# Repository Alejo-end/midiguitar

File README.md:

# MIDI Guitar

A time-of-flight distance sensor embedded in a Squier Mustang electric guitar, turning hand gestures into MIDI messages for controlling effects in Max/MSP, Ableton, or any MIDI host.

## How it works

The system has two halves:

- **Guitar** (`code/tof_midi_v5/`): a VL53L1X sensor near the pickups measures hand distance. The firmware turns distance and hand speed into MIDI CC or 14-bit pitch bend, sends it over USB-MIDI, and broadcasts it over ESP-NOW (WiFi channel 1) to the receiver. A rotary encoder drives a 4-page OLED menu; a 16-LED NeoPixel ring mirrors the values.
- **Receiver dongle** (`code/tof_midi_v6_rx/`): receives the guitar's ESP-NOW stream and re-emits it as USB-MIDI and on a 5-pin DIN MIDI OUT. It also has its own VL53L5CX 8×8 sensor as a second gesture zone, an expression-pedal input and MUTE / HOLD footswitches.

## Firmware

| Folder | Runs on | Status |
|--------|---------|--------|
| **`code/tof_midi_v5/`** | Guitar (`finalMidiGuitar` PCB) | **Current.** USB-MIDI + ESP-NOW TX, 4-page UI, NVS settings, 8 presets, WiFi config page. See its [README](code/tof_midi_v5/README.md). |
| **`code/tof_midi_v6_rx/`** | Receiver dongle | **Current.** ESP-NOW RX → USB + DIN MIDI, local VL53L5CX, expression pedal, footswitches, pairing. |
| `code/tof_midi_v6/` | Receiver dongle | Experimental "Heat" build: mode router (DRONE / RHYTHM / DRUMS), MCP4561 expression output, presets, web config. Untested on hardware; ignores the dongle's expression input and HOLD footswitch. |
| `code/tof_midi_v4/` | Older guitar wiring | Legacy (BLE-MIDI, old pin map). Does **not** match the current PCB. |
| `code/debug/`, `code/debug_oled/` | Guitar PCB | Bring-up diagnostics (peripheral self-test, OLED-only test). |

## Wiring

XIAO ESP32-S3 pad → GPIO: `D0=1 D1=2 D2=3 D3=4 D4=5 D5=6 D6=43 D7=44 D8=7 D9=8 D10=9`

### Guitar (v5, `finalMidiGuitar` PCB)

| Function | XIAO pad | GPIO | Notes |
|----------|----------|------|-------|
| I2C SDA | D4 | 5 | OLED (0x3C) + VL53L1X (0x29), 400 kHz |
| I2C SCL | D5 | 6 | |
| NeoPixel data | D10 | 9 | Through level shifter U1 to the 16-LED ring |
| Encoder A | D8 | 7 | |
| Encoder B | D9 | 8 | |
| Encoder push | D3 | 4 | To GND, INPUT_PULLUP. All gestures are on this push. |
| SW1 | D2 | 3 | Populated but unused (reads stuck LOW on this PCB) |

The VL53L1X stays at its default address 0x29; the board has no XSHUT or INT trace.

### Receiver dongle (v6_rx, rev 2026-10)

| Function | XIAO pad | GPIO | Notes |
|----------|----------|------|-------|
| I2C SDA | D4 | 5 | OLED (0x3C) + VL53L5CX (0x29) [+ MCP4561 0x2E for v6] |
| I2C SCL | D5 | 6 | |
| NeoPixel data | D10 | 9 | Through level shifter to the 8-LED stick |
| Encoder A / B | D8 / D9 | 7 / 8 | |
| Encoder push | D3 | 4 | |
| MODE button S3 | D0 | 1 | To GND |
| MUTE button S4 + footswitch tip | D1 | 2 | To GND |
| Expression pedal wiper | D2 | 3 | ADC, internal pull-down |
| MIDI OUT (DIN) | D6 | 43 | Serial1 TX, 31250 baud |
| HOLD footswitch (ring) | D7 | 44 | To GND |

## Building

Arduino IDE or `arduino-cli`, board **XIAO_ESP32S3**, arduino-esp32 core 3.x.

- **USB Mode: USB-OTG (TinyUSB)** — required for USB-MIDI.
- **USB CDC On Boot: Enabled** for the dongle sketches. With it disabled, `Serial` runs on UART0, whose pins (GPIO 43/44) are the dongle's MIDI OUT and HOLD footswitch.

Libraries (Library Manager): Adafruit NeoPixel, Adafruit SSD1306, Adafruit GFX, plus **SparkFun VL53L1X** for the guitar or **SparkFun VL53L5CX** for the dongle.

```bash
arduino-cli compile -b esp32:esp32:XIAO_ESP32S3:USBMode=default,CDCOnBoot=cdc code/tof_midi_v5/
```

```bash
arduino-cli compile -b esp32:esp32:XIAO_ESP32S3:USBMode=default,CDCOnBoot=cdc code/tof_midi_v6_rx/
```

GitHub Actions (`.github/workflows/compile.yml`) compiles the v5, v6, v6_rx and debug sketches on every push.

After editing `code/tof_midi_v5/web_ui.html`, regenerate the embedded page with `code/tof_midi_v5/tools/build_web_ui.sh`.

## PCB

The guitar board is the KiCad project in `finalMidiGuitar/` (`finalMidiGuitar.kicad_sch`, `finalMidiGuitar.kicad_pcb`), with a STEP export and F.Cu + drill gerbers. `HARDWARE.md` documents an earlier iteration of the design and is out of date.

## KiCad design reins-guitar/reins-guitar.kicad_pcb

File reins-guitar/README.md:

# REINS guitar board for JLCPCB

This is the guitar board of the REINS system, made for JLCPCB. It replaces the milled board in `../finalMidiGuitar/`. These parts stay in the same places, in the same board coordinates: the outline, the four M2 holes, the OLED, the encoder, the button and the USB-C end of the XIAO. The pickguard cutouts and the mounting stay the same.

## What changed from the milled board

1. Two copper layers, a ground pour on both sides and stitching vias.
2. JLCPCB solders the small parts on the top side. The three cable headers stand on the bottom side, so the cables go down into the cavity.
3. A LiPo battery and an on/off switch. D0 reads the battery voltage, and the OLED shows the charge.
4. The LED ring also lights on battery. Two diodes feed it from USB 5 V or from the battery.
5. The button moved from D2 to D1 and uses two diagonal pads. On the milled board, the footprint joined both button pads to one internal contact of the switch. That is why D2 read stuck LOW.
6. The encoder tab slots follow the Bourns PEC12R sheet: 13.2 mm apart, 2.4 x 3.2 mm. The milled board had them 2 mm too close together.
7. The OLED mounting slots are real oval holes, not stacks of round holes.

## Order

Run this command in this folder:

```
/Applications/KiCad/KiCad.app/Contents/Frameworks/Python.framework/Versions/3.9/bin/python3 export_jlc.py
```

It writes `fab/jlc/reins-guitar/` with the Gerber zip, the BOM and the CPL. The steps for the whole REINS order (three boards) are in `heat/kicad/ORDER_JLCPCB.md`.

## Parts that JLCPCB solders

| Parts | LCSC |
| --- | --- |
| U1: SN74LVC1T45DBVR level shifter | C7843 |
| R1: 330 ohm 0603 | C23138 |
| R4, R5: 100k 0603 | C25803 |
| C1, C2, C4, C5: 100 nF 0603 | C14663 |
| C3: 22 uF 25 V 0805 | C45783 |
| D1, D2: B5819W Schottky diode | C8598 |

## Parts that you solder

| Part | Side | Notes |
| --- | --- | --- |
| Two 1x7 female sockets (SMD) for the XIAO | Top | Same sockets as on the milled board |
| OLED module J4 | Top | Pins: GND, VCC, SCL, SDA |
| Encoder S1 (PEC12R-4015F-S0024) | Top | |
| Button SW1 (Omron B3SN) | Top | Any of its four rotations works |
| J1: JST PH 4-pin header B4B-PH-K-S | Bottom | ToF sensor |
| J2: JST PH 2-pin header B2B-PH-K-S | Bottom | Battery |
| J3: JST PH 3-pin header B3B-PH-K-S | Bottom | LED ring |
| Two wires for the on/off switch | J5 pads | For no switch, bridge the two pads with a wire |
| One thin wire from TP1 to BAT+ under the XIAO | TP1 pad | |

Put the headers in from the bottom side and solder them on the top side.

## Cables

| Header | Pin 1 | Pin 2 | Pin 3 | Pin 4 |
| --- | --- | --- | --- | --- |
| J1 ToF sensor | GND | 3V3 | SCL | SDA |
| J2 battery | minus | plus | | |
| J3 LED ring | supply | data in | GND | |

The silkscreen on the bottom side shows the same names next to each header. J1 uses the same pin order as the OLED.

Warning: compare the battery wires with the plus and minus marks before you plug it in. Many LiPo cells come with the wires the other way round. A reversed battery destroys the XIAO.

## Battery and power

1. The battery goes to J2. The switch on J5 is in series with the battery plus wire.
2. Solder a thin wire from TP1 to the BAT+ pad under the XIAO. The XIAO charges the battery over USB-C.
3. The battery charges only while the switch is on.
4. On battery only, the LED ring gets 3.3 to 3.9 V. It dims a little and can flicker near an empty battery. The firmware shows `LOW BAT` at 3.45 V.

## Firmware

`code/tof_midi_v5/tof_midi_v5.ino` reads the button on D1 (mute toggle on every page) and the battery on D0. For the milled board, set `BTN_PIN` and `BAT_PIN` to -1.

## Mechanical notes

1. The holes take M2 screws with heads up to 3.8 mm across. A metal hex standoff on the top side touches the XIAO socket pad next to the top right hole. Use a nylon standoff or a screw head there.
2. The XIAO antenna cable needs to stay outside any metal shielding in the cavity, or the range to the receiver drops.

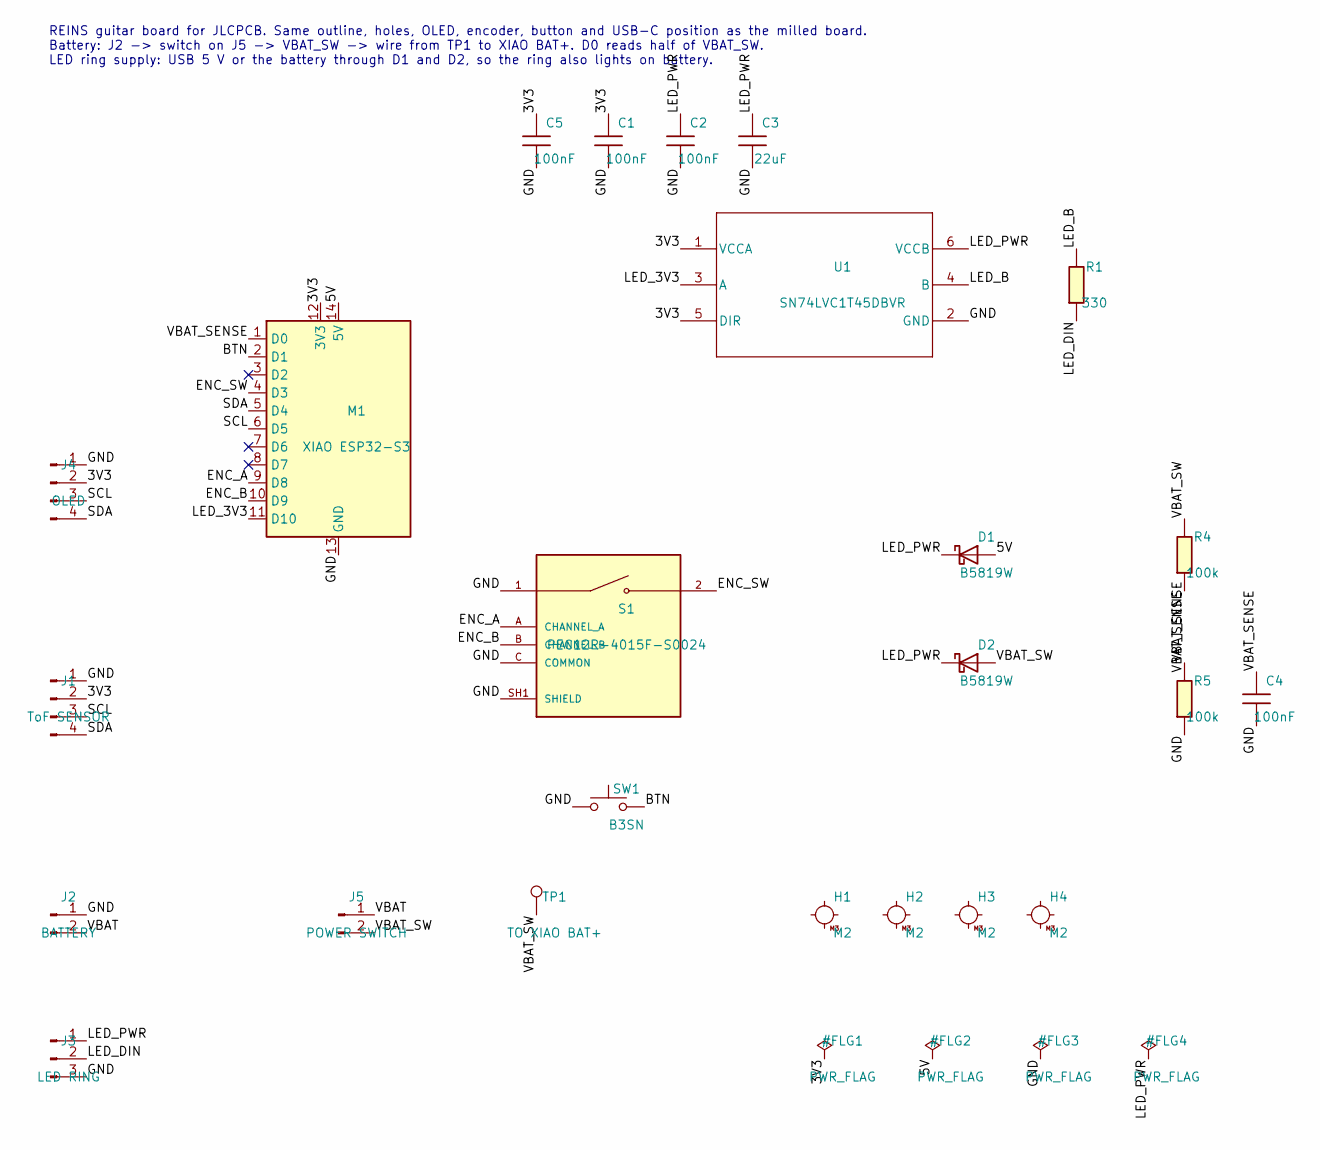
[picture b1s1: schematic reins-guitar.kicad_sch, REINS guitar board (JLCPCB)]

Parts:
C1, C2, C4, C5: 100nF; C_0603_1608Metric; LCSC C14663
C3: 22uF; C_0805_2012Metric; LCSC C45783
D1, D2: B5819W; D_SOD-123; LCSC C8598
H1, H2, H3, H4: M2; MountingHole_2.2mm_M2_Head3.8mm
J1: ToF SENSOR; JST_PH_B4B-PH-K_1x04_P2.00mm_Vertical
J2: BATTERY; JST_PH_B2B-PH-K_1x02_P2.00mm_Vertical
J3: LED RING; JST_PH_B3B-PH-K_1x03_P2.00mm_Vertical
J4: OLED; OLED_SSD1306_0.96in_I2C_THT
J5: POWER SWITCH; WirePads_1x02_P2.54mm
M1: XIAO ESP32-S3; Module_XIAO_Generic_SocketSMD
R1: 330; R_0603_1608Metric; LCSC C23138
R4, R5: 100k; R_0603_1608Metric; LCSC C25803
S1: PEC12R-4015F-S0024; RotaryEncoder_Bourns_PEC12R-4xxxF-S
SW1: B3SN; SW_Omron_B3SN_6x6mm_Diagonal
TP1: TO XIAO BAT+; WirePad_THT_D1.6mm_Drill0.8mm
U1: SN74LVC1T45DBVR; SOT-23-6; LCSC C7843

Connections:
/3V3: C1.1, C5.1, J1.2, J4.2, M1.12 (3V3), U1.1 (VCCA), U1.5 (DIR)
/5V: D1.2 (A), M1.14 (5V)
/BTN: M1.2 (D1), SW1.2
/ENC_A: M1.9 (D8), S1.A (CHANNEL_A)
/ENC_B: M1.10 (D9), S1.B (CHANNEL_B)
/ENC_SW: M1.4 (D3), S1.2
/GND: C1.2, C2.2, C3.2, C4.2, C5.2, J1.1, J2.1, J3.3, J4.1, M1.13 (GND), R5.2, S1.1, S1.C (COMMON), S1.SH1 (SHIELD), S1.SH2 (SHIELD), SW1.1, U1.2 (GND)
/LED_3V3: M1.11 (D10), U1.3 (A)
/LED_B: R1.1, U1.4 (B)
/LED_DIN: J3.2, R1.2
/LED_PWR: C2.1, C3.1, D1.1 (K), D2.1 (K), J3.1, U1.6 (VCCB)
/SCL: J1.3, J4.3, M1.6 (D5)
/SDA: J1.4, J4.4, M1.5 (D4)
/VBAT: J2.2, J5.1
/VBAT_SENSE: C4.1, M1.1 (D0), R4.2, R5.1
/VBAT_SW: D2.2 (A), J5.2, R4.1, TP1.1

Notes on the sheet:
REINS guitar board for JLCPCB. Same outline, holes, OLED, encoder, button and USB-C position as the milled board. Battery: J2 -> switch on J5 -> VBAT_SW -> wire from TP1 to XIAO BAT+. D0 reads half of VBAT_SW. LED ring supply: USB 5 V or the battery through D1 and D2, so the ring also lights on bat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

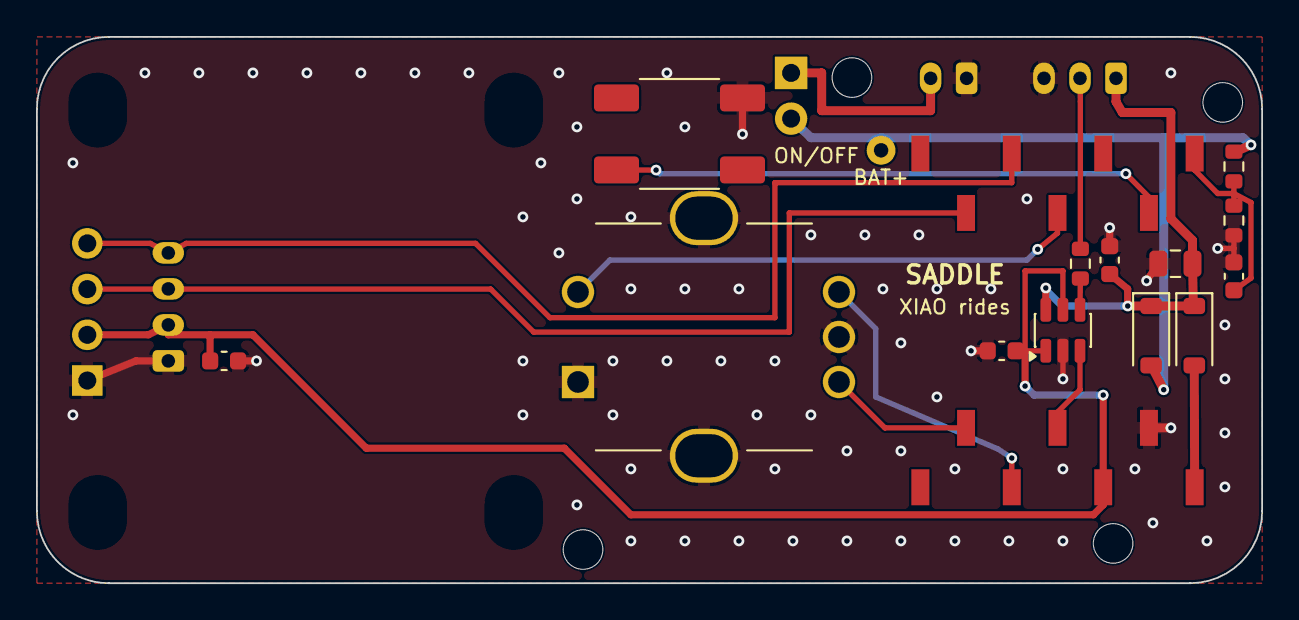
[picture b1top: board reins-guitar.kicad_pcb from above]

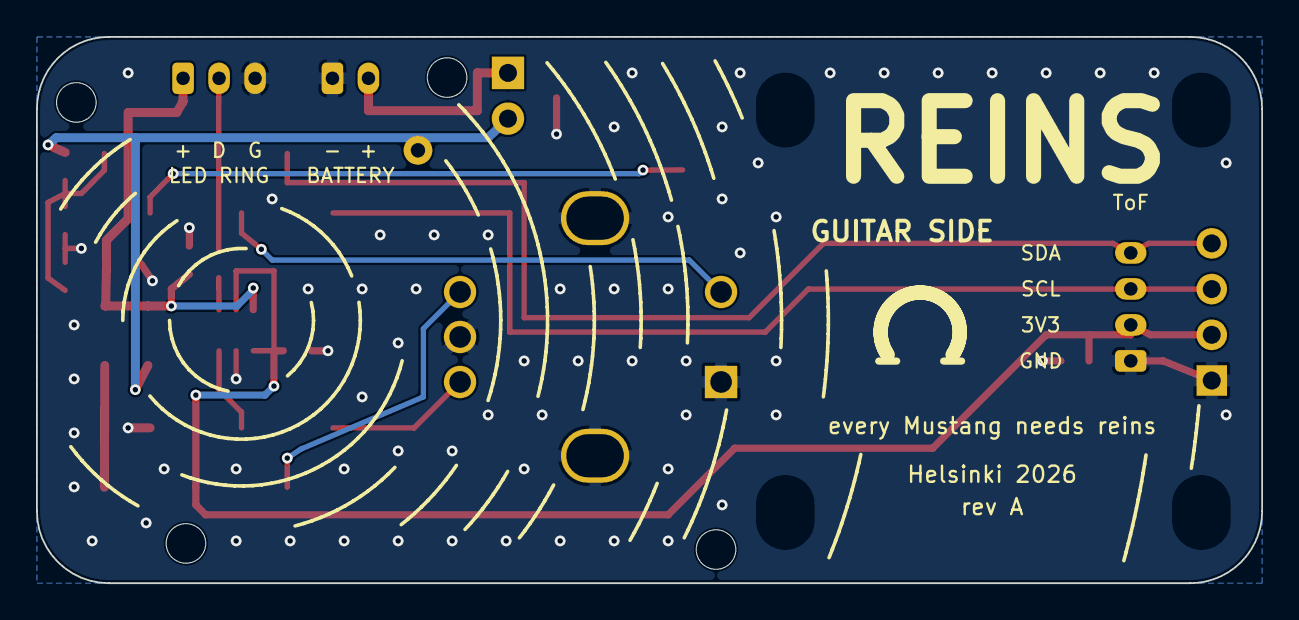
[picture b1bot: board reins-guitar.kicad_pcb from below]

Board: 2 copper layers, 68.1 x 30.3 mm, 24 parts (3 on the bottom side), 16 nets.

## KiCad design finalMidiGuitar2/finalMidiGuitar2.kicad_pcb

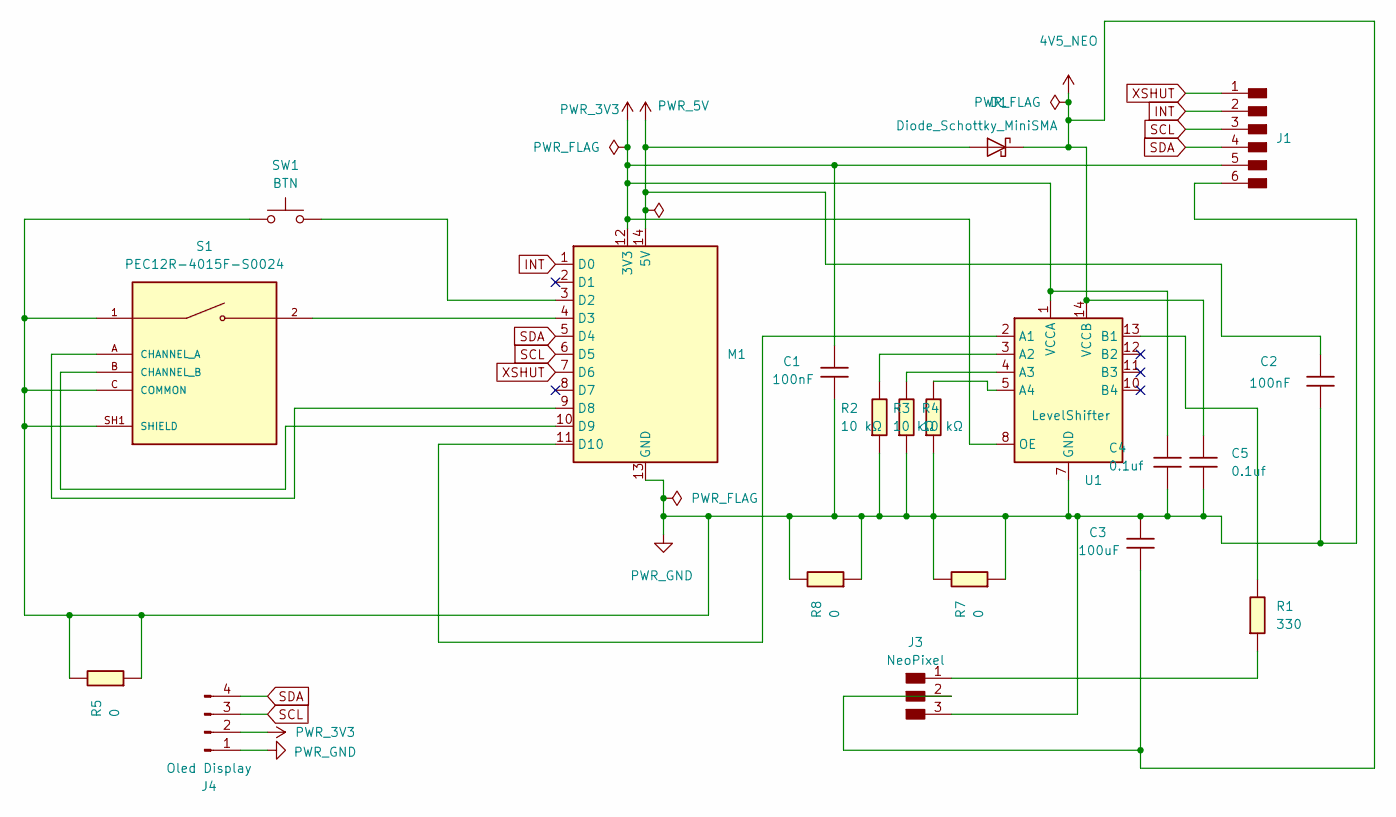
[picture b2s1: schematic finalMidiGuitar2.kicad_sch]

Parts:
C1, C2: 100nF; C_1206
C3: 100uF; C_1206
C4, C5: 0.1uf; C_1206
D1: Diode_Schottky_MiniSMA
J1: PinHeader_01x06_P2.54mm_Vertical_THT_D1mm
J3: NeoPixel; PinHeader_01x03_P2.54mm_Vertical_THT_D1mm
J4: Oled Display; Display_128x64_096_I2C
M1: Module_XIAO_Generic_SocketSMD
R1: 330; R_1206
R2, R3, R4: 10 kΩ; R_1206
R5, R7, R8: 0; R_1206
S1: PEC12R-4015F-S0024; XDCR_PEC12R-4015F-S0024; PARTREV 07/21
SW1: BTN; Button_Omron_B3SN_6.0x6.0mm
U1: LevelShifter; LevelShifter_Texas_TXB0104DR_SOIC-14

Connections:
4V5_NEO: C3.2, C5.1, D1.1 (K), J3.2, U1.14 (VCCB)
INT: J1.2, M1.1 (D0)
unnamed: J3.1, R1.2
unnamed: M1.3 (D2), SW1.2
unnamed: M1.4 (D3), S1.2
unnamed: M1.9 (D8), S1.A (CHANNEL_A)
unnamed: M1.10 (D9), S1.B (CHANNEL_B)
unnamed: M1.11 (D10), U1.2 (A1)
unnamed: R2.1, U1.3 (A2)
unnamed: R3.1, U1.4 (A3)
unnamed: R4.1, U1.5 (A4)
unnamed: R1.1, U1.13 (B1)
PWR_3V3: C1.1, C4.1, J1.5, J4.2, M1.12 (3V3), U1.1 (VCCA), U1.8 (OE)
PWR_5V: C2.1, D1.2 (A), M1.14 (5V)
PWR_GND: C1.2, C2.2, C3.1, C4.2, C5.2, J1.6, J3.3, J4.1, M1.13 (GND), R2.2, R3.2, R4.2, R5.1, R5.2, R7.1, R7.2, R8.1, R8.2, S1.1, S1.C (COMMON), S1.SH1 (SHIELD), S1.SH2 (SHIELD), SW1.1, U1.7 (GND)
SCL: J1.3, J4.3, M1.6 (D5)
SDA: J1.4, J4.4, M1.5 (D4)
XSHUT: J1.1, M1.7 (D6)

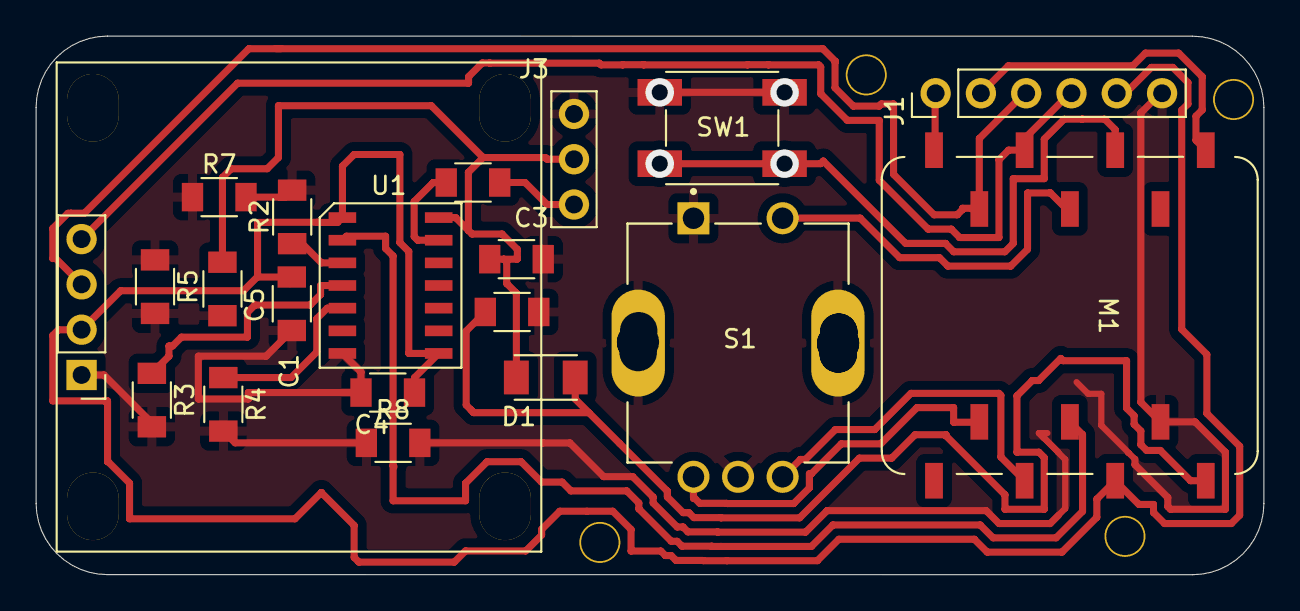
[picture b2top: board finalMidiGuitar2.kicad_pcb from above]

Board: 2 copper layers, 68.9 x 30.2 mm, 20 parts (0 on the bottom side), 18 nets.

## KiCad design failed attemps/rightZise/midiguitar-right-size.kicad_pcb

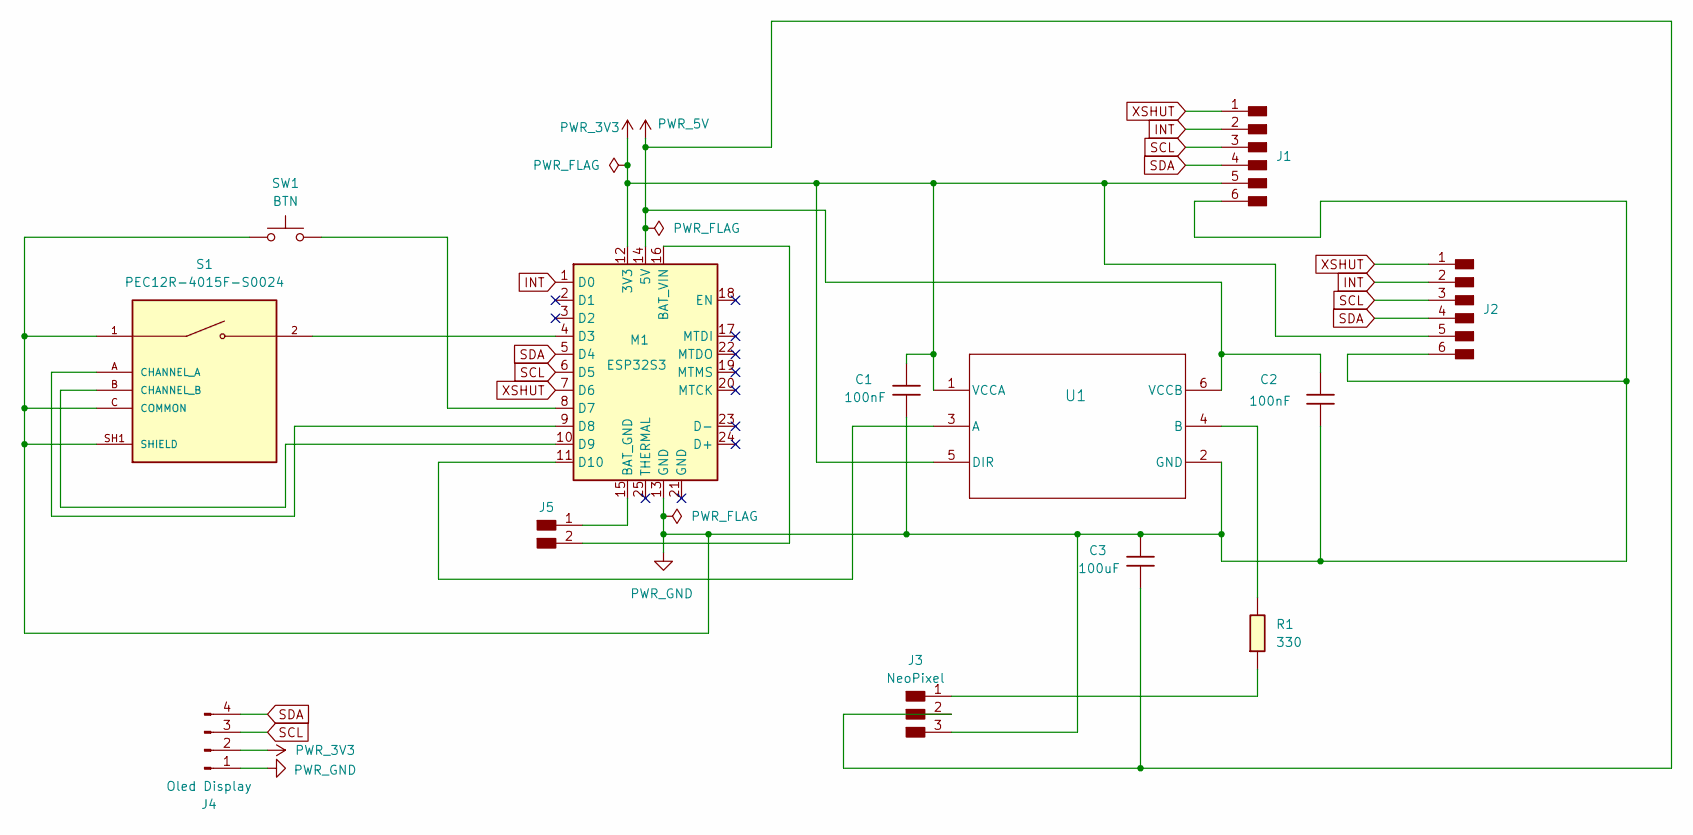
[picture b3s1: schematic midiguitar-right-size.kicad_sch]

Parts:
C1, C2: 100nF; C_1206
C3: 100uF; C_1206
J1, J2: PinHeader_01x06_P2.54mm_Vertical_THT_D1mm
J3: NeoPixel; PinHeader_01x03_P2.54mm_Vertical_THT_D1mm
J4: Oled Display; Display_128x64_096_I2C
J5: PinHeader_01x02_P2.54mm_Vertical_THT_D1mm
M1: ESP32S3; SeeedStudio_XIAO_ESP32S3
R1: 330; R_1206
S1: PEC12R-4015F-S0024; XDCR_PEC12R-4015F-S0024; PARTREV 07/21
SW1: BTN; Button_Omron_B3SN_6.0x6.0mm
U1: SN74LVC1T45DBVR; DBV0006A_N

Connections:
INT: J1.2, J2.2, M1.1 (D0)
unnamed: J3.1, R1.2
unnamed: J5.1, M1.15 (BAT_GND)
unnamed: J5.2, M1.16 (BAT_VIN)
unnamed: M1.4 (D3), S1.2
unnamed: M1.8 (D7), SW1.2
unnamed: M1.9 (D8), S1.A (CHANNEL_A)
unnamed: M1.10 (D9), S1.B (CHANNEL_B)
unnamed: M1.11 (D10), U1.3 (A)
unnamed: R1.1, U1.4 (B)
PWR_3V3: C1.1, J1.5, J2.5, J4.2, M1.12 (3V3), U1.1 (VCCA), U1.5 (DIR)
PWR_5V: C2.1, C3.2, J3.2, M1.14 (5V), U1.6 (VCCB)
PWR_GND: C1.2, C2.2, C3.1, J1.6, J2.6, J3.3, J4.1, M1.13 (GND), M1.21 (GND), S1.1, S1.C (COMMON), S1.SH1 (SHIELD), S1.SH2 (SHIELD), SW1.1, U1.2 (GND)
SCL: J1.3, J2.3, J4.3, M1.6 (D5)
SDA: J1.4, J2.4, J4.4, M1.5 (D4)
XSHUT: J1.1, J2.1, M1.7 (D6)

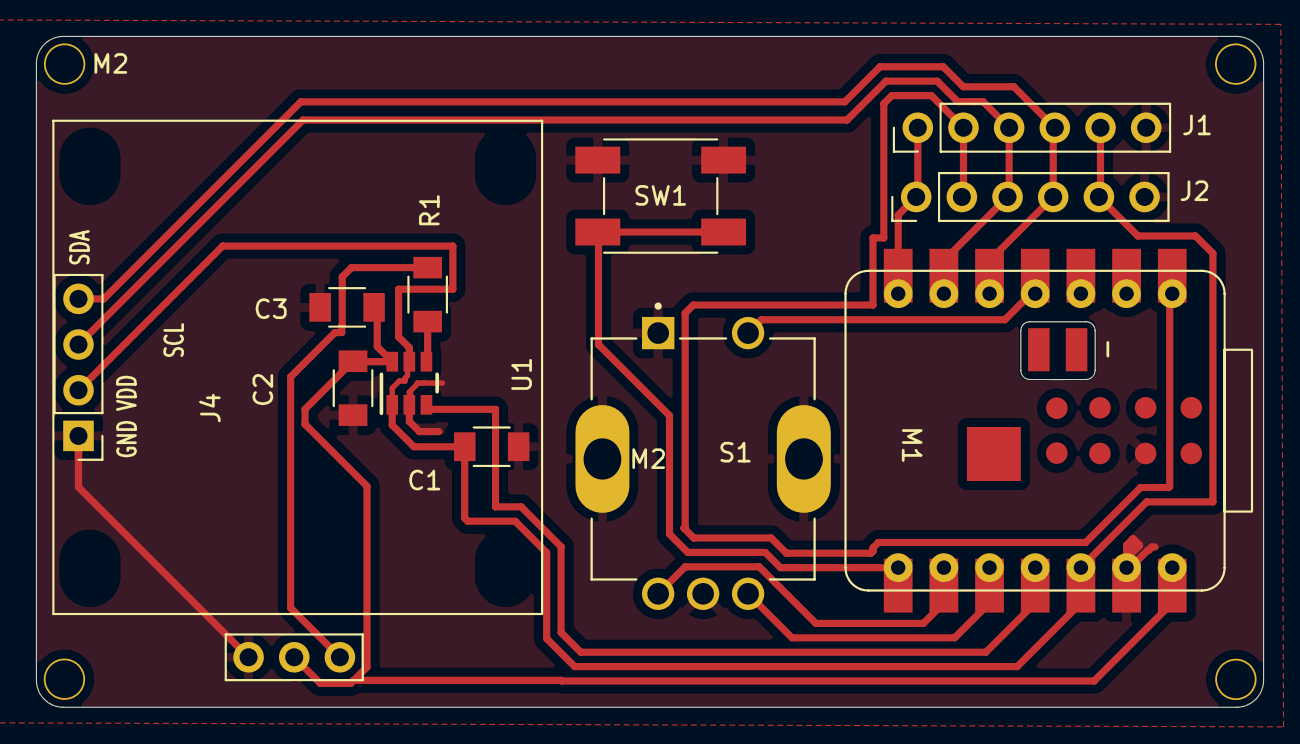
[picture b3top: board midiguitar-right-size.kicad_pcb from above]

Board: 2 copper layers, 68.2 x 37.3 mm, 12 parts (0 on the bottom side), 14 nets.

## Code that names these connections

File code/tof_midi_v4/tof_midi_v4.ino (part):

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// Hardware pins & constants (true compile-time)
#define BLE_NAME        "MidiGuitar"
#define VL53_ADDR       0x30
#define XSHUT_VL53      5       // D4  — VL53L1X XSHUT
#define VL53_INT        9       // D10 — VL53L1X data-ready interrupt
#define POLL_MS         20
#define EMA_ALPHA       0.2f
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#define CURVE_EXP       2
#define STRIP_PIN       1       // D0  — level-shifted via U1 to NeoPixel header (J3)
#define BTN_EDIT        7       // D8  — SW1 tactile button to GND
#define ENC_A           3       // D2  — S1 rotary encoder channel A
#define ENC_B           2       // D1  — S1 rotary encoder channel B
#define ENC_PUSH        44      // D7  — S1 encoder push switch to GND
#define NUM_PIXELS      16
#define OLED_W          128
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    loadSettings();

    pinMode(BTN_EDIT, INPUT_PULLUP);
    pinMode(ENC_A, INPUT_PULLUP);
    pinMode(ENC_B, INPUT_PULLUP);
    pinMode(ENC_PUSH, INPUT_PULLUP);
    attachInterrupt(digitalPinToInterrupt(ENC_A), encISR, CHANGE);
    attachInterrupt(digitalPinToInterrupt(ENC_B), encISR, CHANGE);

    USB.enableDFU();
    usbMidi.begin();
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
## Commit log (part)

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2026-04-01 Refactor tof_midi.ino for improved clarity and organization; update comments and streamline sensor initialization
2026-04-02 Refactor code structure for improved readability and maintainability
2026-04-02 Add README.md for MIDI guitar project overview, usage, hardware details, and configuration
2026-04-02 Update README.md for enhanced clarity and detail; refine hardware and wiring sections, and improve MIDI output descriptions.
2026-04-02 Enhance README.md with detailed system overview and signal flow diagrams; add pickguard layout for better hardware understanding.
2026-04-02 Remove system overview and signal flow diagrams from README.md for simplification
2026-04-04 Updated `midiguitar.kicad_pro` with detailed design settings and Introduced a new symbol library table in `sym-lib-table` for `midiguitar-eagle-import`.
2026-04-04 Refactor MIDI control change function to use 1-based channel indexing in tof_midi and tof_midi_v2
2026-04-07 Remove lock files for midiguitar project to clean up workspace
2026-04-09 Add ToF MIDI controller with visual UI and BLE support
2026-04-10 Update README.md with enhanced descriptions of MIDI output, hardware components, GPIO pinout, and user interface features
2026-04-12 Update sym-lib-table version to 7 for midiguitar-eagle-import library
2026-04-14 Refactor button and transport pin definitions; remove bypass functionality
2026-04-15 Add sensor interrupt handling and enhance button functionality for context-sensitive actions
2026-04-20 Update pad dimensions and clean up schematic and pcb
2026-04-20 Refactor hardware pin definitions for clarity and consistency
2026-04-23 Add lock files for PCB and schematic in finalMidiGuitar2 project
2026-04-24 Remove lock files for KiCad PCB and schematic
2026-04-26 Add new CAD and backup files for Midi Guitar project
2026-05-04 Add finalMidiGuitar.step file to the project
2026-05-04 Add web UI HTML and build script for MIDI Guitar interface
    - Introduced `web_ui.html` as the main HTML file for the MIDI Guitar interface, including layout and styling.
    - Created `build_web_ui.sh` script to generate a header file `web_ui_html.h` from `web_ui.html`, stripping unnecessary comments and wrapping the content in a PROGMEM raw-string for ESP32 compatibilit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
    - The script ensures that the generated header file is automatically updated when changes are made to the HTML source.
2026-05-05 Add label "Midi Guitar" to the schematic for better identification
2026-05-08 Add detailed documentation for networking and communication features in MIDI Guitar
2026-05-15 Update README and code comments for clarity on encoder gestures and WiFi config
2026-06-15 add v6 version for receiver
